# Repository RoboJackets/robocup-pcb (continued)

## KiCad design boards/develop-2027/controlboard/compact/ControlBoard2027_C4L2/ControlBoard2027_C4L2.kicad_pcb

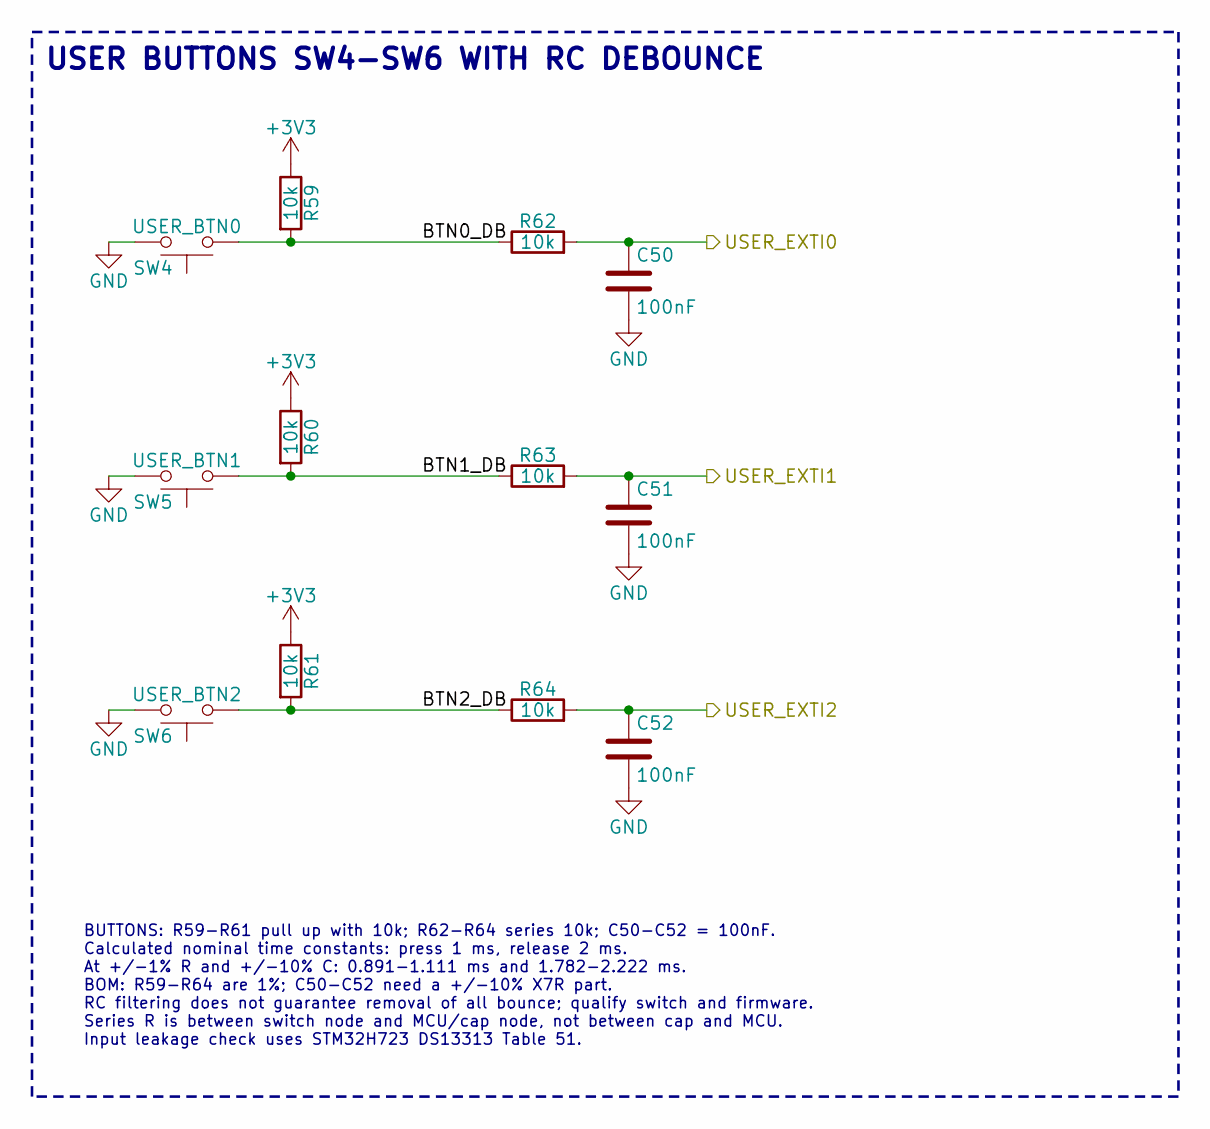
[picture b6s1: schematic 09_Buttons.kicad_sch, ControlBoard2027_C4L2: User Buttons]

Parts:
C50, C51, C52: 100nF; C_0402_1005Metric; Rating 16V X7R; MPN Samsung CL05B104KO5NNNC; LCSC C1525
R59, R60, R61, R62, R63, R64: 10k; R_0603_1608Metric; Rating 1%; MPN Panasonic ERJ-3EKF1002V; LCSC C25804
SW4: USER_BTN0; SW_PUSH_1P1T_6x3.5mm_H4.3_APEM_MJTP1243; MPN APEM MJTP1243; LCSC C2689636
SW5: USER_BTN1; SW_PUSH_1P1T_6x3.5mm_H4.3_APEM_MJTP1243; MPN APEM MJTP1243; LCSC C2689636
SW6: USER_BTN2; SW_PUSH_1P1T_6x3.5mm_H4.3_APEM_MJTP1243; MPN APEM MJTP1243; LCSC C2689636

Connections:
+3V3: R59.1, R60.1, R61.1; also elsewhere on the board
/MCU/USER_EXTI0: C50.1, R62.2; also elsewhere on the board
/MCU/USER_EXTI1: C51.1, R63.2; also elsewhere on the board
/MCU/USER_EXTI2: C52.1, R64.2; also elsewhere on the board
/User Buttons/BTN0_DB: R59.2, R62.1, SW4.1
/User Buttons/BTN1_DB: R60.2, R63.1, SW5.1
/User Buttons/BTN2_DB: R61.2, R64.1, SW6.1

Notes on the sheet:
BUTTONS: R59-R61 pull up with 10k; R62-R64 series 10k; C50-C52 = 100nF. Calculated nominal time constants: press 1 ms, release 2 ms. At +/-1% R and +/-10% C: 0.891-1.111 ms and 1.782-2.222 ms. BOM: R59-R64 are 1%; C50-C52 need a +/-10% X7R part. RC filtering does not guarantee removal of all bounce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
USER BUTTONS SW4-SW6 WITH RC DEBOUNCE

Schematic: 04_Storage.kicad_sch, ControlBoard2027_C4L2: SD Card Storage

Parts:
C1: 10uF; C_0603_1608Metric; Rating 10V X5R 10%; MPN Taiyo Yuden LMK107BBJ106MALT; LCSC C19702
C2: 100nF; C_0402_1005Metric; Rating 16V X7R; MPN Samsung CL05B104KO5NNNC; LCSC C1525
J1: microSD_SDIO; microSD_HC_Hirose_DM3AT-SF-PEJM5; MPN Hirose DM3AT-SF-PEJM5; LCSC C114218
R1, R2, R3, R4, R5, R73: 47k; R_0402_1005Metric; Rating 1%; MPN Yageo RC0402FR-0747KL; LCSC C25792
R6: 30R; R_0402_1005Metric; Rating 1%; MPN Stackpole RMCF0402FT30R0; LCSC C2479340
TP1: SD_CLK; TestPoint_Pad_1.0x1.0mm
U1: TPD6E05U06RVZ; Texas_R-PUSON-N14; MPN TPD6E05U06RVZR; LCSC C962978

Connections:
+3V3: C1.1, C2.1, J1.4 (VDD), R1.1, R2.1, R3.1, R4.1, R5.1, R73.1; also elsewhere on the board
/MCU/SDMMC_CK: R6.1; also elsewhere on the board
/MCU/SD_DET: J1.9 (DET_B), R73.2; also elsewhere on the board
/SD Card Storage/SDMMC_CMD: J1.3 (CMD), R3.2, U1.3 (NC), U1.12 (D2+); also elsewhere on the board
/SD Card Storage/SDMMC_D0: J1.7 (DAT0), R4.2, U1.6 (NC), U1.9 (D3+); also elsewhere on the board
/SD Card Storage/SDMMC_D1: J1.8 (DAT1), R5.2, U1.7 (NC), U1.8 (D3-); also elsewhere on the board
/SD Card Storage/SDMMC_D2: J1.1 (DAT2), R1.2, U1.1 (NC), U1.14 (D1+); also elsewhere on the board
/SD Card Storage/SDMMC_D3: J1.2 (DAT3/CD), R2.2, U1.2 (NC), U1.13 (D1-); also elsewhere on the board
/SD Card Storage/SD_CLK_CARD: J1.5 (CLK), R6.2, TP1.1 (1_1), U1.4 (NC), U1.11 (D2-)

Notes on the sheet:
SD ESD U1 AT J1, CLK TEST POINT
MICROSD J1 ON SDMMC2 4-BIT, CARD DETECT R73
SDMMC LAYOUT: review CLK, CMD and DAT0-3 as one timing interface. Routed 50R on L1 over L2 GND and on L4 over an L3 GND island; CLK/CMD/DAT0-3 67.08-67.66 mm incl. R6 (worst 0.47 mm vs CLK). Keep return paths continuous, short stubs and local J1 bypass capacitors. Use DS13313 SDMMC timing plus the 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
SD CARD: select an actual card MPN before final timing approval. Kingston SDCIT example: identification clock <=400 kHz, NOT 8 MHz. Higher transfer rates require successful initialization and timing validation. J1 Hirose DM3AT-SF-PEJM5. Shell to GND; power cannot be cycled independently. Card detec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
R6 = 30R provisional CLK source damping near PD6. CMD and DAT0-3 currently have no series damping; check both directions. 47k pull-ups are bias, not impedance termination. No data sheet establishes a constant 25R MCU output impedance.

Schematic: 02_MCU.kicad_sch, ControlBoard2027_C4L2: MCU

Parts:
C3, C4, C6, C8, C9, C10, C12, C13, C14, C15, C16, C17, C20, C21, C25, C27: 100nF; C_0402_1005Metric; Rating 16V X7R; MPN Samsung CL05B104KO5NNNC; LCSC C1525
C5: 10uF 10V X5R; C_0603_1608Metric; Rating 10V X5R 10%; MPN Taiyo Yuden LMK107BBJ106MALT; LCSC C19702
C7, C11: 4.7uF 16V X5R; C_0603_1608Metric; Rating 16V X5R; MPN TDK C1608X5R1C475K080AC; LCSC C19666
C18, C19: 12pF; C_0402_1005Metric; Rating 50V C0G; MPN Samsung CL05C120JB5NNNC; LCSC C1547
C22, C23: 2.2uF; C_0603_1608Metric; Rating 10V X7R; MPN Samsung CL10B225KP8NNNC; LCSC C100082
C24, C26: 1uF 50V X5R; C_0603_1608Metric; Rating 50V X5R; MPN Samsung CL10A105KP8NNNC; LCSC C15849
R7, R8, R9, R10, R14, R17, R18, R19: 2.2k; R_0402_1005Metric; Rating 1%; MPN Yageo RC0402FR-072K2L; LCSC C25879
R11, R13: 10k; R_0402_1005Metric; Rating 1%; MPN Yageo RC0402FR-0710KL; LCSC C25744
R12: 0R; R_0402_1005Metric; Rating 0R jumper; MPN Stackpole RMCF0402ZT0R00; LCSC C17168
R15, R16, R65, R66, R67, R68, R70, R71: 30R; R_0402_1005Metric; Rating 1%; MPN Stackpole RMCF0402FT30R0; LCSC C2479340
R20: 47k; R_0402_1005Metric; Rating 1%; MPN Yageo RC0402FR-0747KL; LCSC C25792
R21: 68k; R_0402_1005Metric; Rating 1%; MPN Vishay CRCW040268K0FKED; LCSC C482226
TP2: TP_VDDA; TestPoint_Pad_1.0x1.0mm
U2: STM32H723ZGT6; LQFP-144_20x20mm_P0.5mm; MPN ST STM32H723ZGT6; LCSC C730146
X1: 25MHz 10pF; Crystal_SMD_3225-4Pin_3.2x2.5mm; MPN Abracon ABM8-25.000MHZ-10-B1U-T; LCSC C5366868

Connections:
+3V3: C3.1, C4.1, C5.1, C6.1, C7.1, C8.1, C9.1, C10.1, C11.1, C12.1, C13.1, C14.1, C15.1, C16.1, C17.1, C21.1, C24.1, C25.1, C26.1, C27.1, R7.1, R8.1, R9.1, R10.1, R13.2, R14.1, R17.1, R18.1, R19.1, TP2.1 (1_1), U2.6 (VBAT), U2.17 (VDD), U2.30 (VDD), U2.32 (VREF+), U2.33 (VDDA), U2.39 (VDD), U2.52 (VDD), U2.62 (VDD), U2.72 (VDD), U2.84 (VDD), U2.95 (VDD33USB), U2.108 (VDD), U2.121 (VDD), U2.131 (VDD), U2.143 (PDR_ON), U2.144 (VDD); also elsewhere on the board
/DotStar LEDs/LED_SPI_MOSI: R71.1; also elsewhere on the board
/DotStar LEDs/LED_SPI_SCK: R70.1; also elsewhere on the board
/IMU/ACCEL_EXTI: U2.13 (PF3); also elsewhere on the board
/IMU/GYRO_EXTI: U2.12 (PF2); also elsewhere on the board
/IMU/IMU_I2C_SCL: R10.2, U2.81 (PD12); also elsewhere on the board
/IMU/IMU_I2C_SDA: R8.2, U2.82 (PD13); also elsewhere on the board
/MCU/BOOT0: R11.1, U2.138 (BOOT0); also elsewhere on the board
/MCU/DBG_UART_RX: U2.97 (PC7); also elsewhere on the board
/MCU/DBG_UART_TX: U2.96 (PC6); also elsewhere on the board
/MCU/DIP0: U2.58 (PE7); also elsewhere on the board
/MCU/DIP1: U2.59 (PE8); also elsewhere on the board
/MCU/DIP2: U2.60 (PE9); also elsewhere on the board
/MCU/DIP3: U2.63 (PE10); also elsewhere on the board
/MCU/DIP4: U2.67 (PE14); also elsewhere on the board
/MCU/DIP5: U2.68 (PE15); also elsewhere on the board
/MCU/DRIBBLER_SPI_CS: U2.115 (PD1); also elsewhere on the board
/MCU/ESP_DATA_READY: U2.136 (PB6); also elsewhere on the board
/MCU/ESP_HANDSHAKE: U2.137 (PB7); also elsewhere on the board
/MCU/ESP_MOSI_MCU: R66.1, U2.135 (PB5)
/MCU/ESP_RST: U2.142 (PE1); also elsewhere on the board
/MCU/ESP_SPI_CS: U2.132 (PG15); also elsewhere on the board
/MCU/ESP_SPI_MISO: U2.134 (PB4_NJTRST); also elsewhere on the board
/MCU/ESP_SPI_MOSI: R66.2; also elsewhere on the board
/MCU/ESP_SPI_SCK: R65.2; also elsewhere on the board
/MCU/EXPANSION_SCL: R7.2, U2.11 (PF1); also elsewhere on the board
/MCU/EXPANSION_SDA: R9.2, U2.10 (PF0); also elsewhere on the board
/MCU/KICKER_I2C_SCL: R14.2, U2.139 (PB8); also elsewhere on the board
/MCU/KICKER_I2C_SDA: R17.2, U2.140 (PB9); also elsewhere on the board
/MCU/LED_MOSI_MCU: R71.2, U2.43 (PA7)
/MCU/LED_SCK_MCU: R70.2, U2.41 (PA5)
/MCU/MOTOR0_SPI_CS: U2.114 (PD0); also elsewhere on the board
/MCU/MOTOR1_SPI_CS: U2.73 (PB12); also elsewhere on the board
/MCU/MOTOR2_SPI_CS: U2.77 (PD8); also elsewhere on the board
/MCU/MOTOR3_SPI_CS: U2.116 (PD2); also elsewhere on the board
/MCU/MOTOR_R_SPI_MISO: U2.75 (PB14); also elsewhere on the board
/MCU/MOTOR_R_SPI_MOSI: R68.2; also elsewhere on the board
/MCU/MOTOR_R_SPI_SCK: R67.2; also elsewhere on the board
/MCU/MOTOR_SPI_MISO: U2.112 (PC11); also elsewhere on the board
/MCU/MOTOR_SPI_MOSI: R16.2; also elsewhere on the board
/MCU/MOTOR_SPI_SCK: R15.2; also elsewhere on the board
/MCU/NRST: C20.1, U2.25 (NRST); also elsewhere on the board
/MCU/OLED_I2C_SCL: R18.2, U2.100 (PA8); also elsewhere on the board
/MCU/OLED_I2C_SDA: R19.2, U2.99 (PC9); also elsewhere on the board
/MCU/PWR_SRC_3V3: U2.3 (PE4); also elsewhere on the board
/MCU/PWR_SRC_5V: U2.4 (PE5); also elsewhere on the board
/MCU/PWR_UART_RX: U2.1 (PE2); also elsewhere on the board
/MCU/PWR_UART_TX: U2.2 (PE3); also elsewhere on the board
/MCU/SDMMC_CK: U2.122 (PD6); also elsewhere on the board
/MCU/SD_DET: U2.119 (PD5); also elsewhere on the board
/MCU/SWCLK: U2.109 (PA14_SWCLK); also elsewhere on the board
/MCU/SWDIO: U2.105 (PA13_SWDIO); also elsewhere on the board
/MCU/USER_EXTI0: U2.80 (PD11); also elsewhere on the board
/MCU/USER_EXTI1: U2.85 (PD14); also elsewhere on the board
/MCU/USER_EXTI2: U2.86 (PD15); also elsewhere on the board
/MCU/VBUS_SENSE: R20.2, R21.1, U2.101 (PA9)
/SD Card Storage/SDMMC_CMD: U2.123 (PD7); also elsewhere on the board
/SD Card Storage/SDMMC_D0: U2.124 (PG9); also elsewhere on the board
/SD Card Storage/SDMMC_D1: U2.125 (PG10); also elsewhere on the board
/SD Card Storage/SDMMC_D2: U2.126 (PG11); also elsewhere on the board
/SD Card Storage/SDMMC_D3: U2.127 (PG12); also elsewhere on the board
/USB and Debug/USB_DM: U2.103 (PA11); also elsewhere on the board
/USB and Debug/USB_DP: U2.104 (PA12); also elsewhere on the board
unnamed: C19.1, R12.1, X1.3
unnamed: C22.1, C23.1, U2.71 (VCAP), U2.106 (VCAP)
unnamed: R13.1, U2.110 (PA15_JTDI)
unnamed: R65.1, U2.133 (PB3_SWO)
unnamed: R67.1, U2.74 (PB13)
unnamed: R68.1, U2.76 (PB15)
unnamed: R15.1, U2.111 (PC10)
unnamed: R16.1, U2.113 (PC12)
unnamed: C18.1, U2.23 (PH0), X1.1
unnamed: R12.2, U2.24 (PH1)
VBUS: R20.1; also elsewhere on the board

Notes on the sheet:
VDD33USB p95 (C11+C13) USB FS PHY - keep both close
VDD p30
VBUS SENSE
MCU U2 STM32H723ZGT6 WITH ITS PIN-SIDE PARTS (VCAP, RESET / BOOT0, I2C PULL-UPS, SERIES R)
VDD p17
VDDA p33 (C24+C25)
VDD p131
HSE 25MHZ CRYSTAL
CLOCK: X1 = 25 MHz; set firmware clock tree to the fitted part. R12 = 0R is an oscillator drive-tuning link, not line termination. C18/C19 need measured stray capacitance to establish the 10 pF load. Startup margin and crystal drive remain unverified (ABM8, DS13313 HSE data). No blanket claim that 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
R15/R16 = 30R: provisional source damping, not certified matching. No fixed driver resistance or 55R target follows from DS13313 Tables 52/54. Validate SCK/MOSI/MISO/CS at every cable receiver, both directions.
VDD p84
VDDA p33 and VREF+ p32 use +3V3. Separate local bypass pairs; analog noise must be measured. Source: DS13313 supply scheme / electrical characteristics.
VDD p52
VBAT p6
VREF+ p32 (C26+C27)
VDD DECOUPLING (EACH CAP AT ITS PIN)
VDD p39
VDD p62
VDDA / VREF+ DECOUPLING
ROUTING - HSE CRYSTAL X1, C18, C19 within 5mm of PH0/PH1. Short equal OSC traces, GND guard ring. Nothing routed under or beside the loop.
I2C: R7/R9, R8/R10, R14/R17, R18/R19 are each 2.2k. At 3.3 V: (3.3-0.4)/2.2k = 1.32 mA sink requirement. For a 300 ns rise-time limit: C <= 300ns/(0.8473R) = 161 pF nominal. At +1% R: 159 pF. Include ESD, pins, cables and parallel pull-ups. LSM6DSV32X / SSD1306 / DS13313 timing and I/O data; extern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
VDD p108
ROUTING - DECOUPLING: each cap beside the STM32 pin named under it, via straight to GND. C22/C23 (VCAP) tight to p71/p106. The netlist does not keep this pairing.
VDD bulk (C5+C7) not pin-specific
ROUTING - MOTOR SPI (6 Mbit/s; SPI3 front J4/J8/J7, SPI2 rear J5/J6) R15/R16 within 5mm of PC10/PC12, R67/R68 of PB13/PB15, not at the connectors.
I2C VALIDATION REQUIRED: measure SDA and SCL at worst load. Change to 1.5k only if the rise time exceeds 300 ns, and recheck every device's VOL/current. OLED module pull-ups and expansion-device specifications are not established.
VDD p72
VDD p121
VDD p144

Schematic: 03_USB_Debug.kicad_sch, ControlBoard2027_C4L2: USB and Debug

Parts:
D1: TVS0500DRV; WSON-6-1EP_2x2mm_P0.65mm_EP1x1.6mm; MPN TI TVS0500DRVR; LCSC C609571
F1: PTC 0.75A 1812; Fuse_Bourns_MF-MSMF_1812; MPN Bourns MF-MSMF075/16X-2; LCSC C207065
J2: USB-C_DFU; USB_C_Receptacle_GCT_USB4110; MPN GCT USB4110-GF-A; LCSC C5143397
J3: STDC14; PinHeader_2x07_P1.27mm_Vertical_SMD; MPN Samtec FTSH-107-01-L-DV-K; LCSC C5307809
R22, R23: 5.1k; R_0402_1005Metric; Rating 1%; MPN Yageo RC0402FR-075K1L; LCSC C25905
SW1: RESET; SW_PUSH_1P1T_6x3.5mm_H4.3_APEM_MJTP1243; MPN APEM MJTP1243; LCSC C2689636
SW2: BOOT0_DFU; SW_PUSH_1P1T_6x3.5mm_H4.3_APEM_MJTP1243; MPN APEM MJTP1243; LCSC C2689636
TP3: TP_VBUS; TestPoint_Pad_1.0x1.0mm
U3: TPD4E05U06DQA; USON-10_2.5x1.0mm_P0.5mm; MPN TI TPD4E05U06DQAR; LCSC C138714

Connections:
+3V3: J3.3 (VCC), SW2.2; also elsewhere on the board
/MCU/BOOT0: SW2.1; also elsewhere on the board
/MCU/DBG_UART_RX: J3.13 (VCP_RX); also elsewhere on the board
/MCU/DBG_UART_TX: J3.14 (VCP_TX); also elsewhere on the board
/MCU/NRST: J3.12 (~RST), SW1.1; also elsewhere on the board
/MCU/SWCLK: J3.6 (JCLK/SWCLK); also elsewhere on the board
/MCU/SWDIO: J3.4 (JTMS/SWDIO); also elsewhere on the board
/USB and Debug/CC1: J2.A5 (CC1), R23.1
/USB and Debug/CC2: J2.B5 (CC2), R22.1
/USB and Debug/USB_DM: J2.A7 (D-), J2.B7 (D-), U3.2 (D1-), U3.5 (D2-), U3.6 (NC), U3.9 (NC); also elsewhere on the board
/USB and Debug/USB_DP: J2.A6 (D+), J2.B6 (D+), U3.1 (D1+), U3.4 (D2+), U3.7 (NC), U3.10 (NC); also elsewhere on the board
unnamed: D1.4 (IN), D1.5 (IN), D1.6 (IN), F1.2, J2.A4 (VBUS), J2.A9 (VBUS), J2.B4 (VBUS), J2.B9 (VBUS)
VBUS: F1.1, TP3.1 (1_1); also elsewhere on the board

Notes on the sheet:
USB LOAD: F1 PTC Ihold = 0.75 A at 20-23C, 0.55 A at 50C. Actual concurrent worst-case board/external current is not established. Restricted bench use until host current, startup and thermal budget are checked. F1 does not negotiate USB current; replacing it alone cannot approve more load.
USB-C J2: TVS, FUSE, CC RESISTORS, ESD
SWD is direct; damping depends on probe/cable edges and layout. DS13313 does not prescribe a universal 22R or 55R series resistor. NRST has an internal 30-50k pull-up; C20 = 100nF (DS13313 NRST data). U3 TPD4E05U06 has no supply pin (no rail injection); GND pins 3/8 to vias.
SWD: J3 STDC14; RESET AND BOOT BUTTONS
USB LAYOUT: keep DP/DM coupled over an uninterrupted ground reference. U3 flow-through at J2: A6/B6 (D+) and A7/B7 (D-) each pass U3 before any via; the duplicates join after U3. Impedance/skew depend on stackup, not series R. TPD4E05U06 layout: flow-through, short GND vias. 90R pair over L2 GND.

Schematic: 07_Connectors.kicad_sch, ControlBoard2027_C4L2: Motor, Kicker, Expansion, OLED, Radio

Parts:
C28: 22uF; C_0805_2012Metric; Rating 25V X5R 20%; MPN Samsung CL21A226MOQNNNE; LCSC C45783
C29: 100nF; C_0402_1005Metric; Rating 16V X7R; MPN Samsung CL05B104KO5NNNC; LCSC C1525
F3, F4: PTC 0.75A 1812; Fuse_Bourns_MF-MSMF_1812; MPN Bourns MF-MSMF075/16X-2; LCSC C207065
H1, H2, H3, H4: MountingHole; MountingHole_3.2mm_M3
H5, H6: MountingHole; MountingHole_2.2mm_M2
J4: MOTOR0; JST_GH_SM06B-GHS-TB_1x06-1MP_P1.25mm_Horizontal; MPN JST SM06B-GHS-TB(LF)(SN); LCSC C133065
J5: MOTOR1; JST_GH_SM06B-GHS-TB_1x06-1MP_P1.25mm_Horizontal; MPN JST SM06B-GHS-TB(LF)(SN); LCSC C133065
J6: MOTOR2; JST_GH_SM06B-GHS-TB_1x06-1MP_P1.25mm_Horizontal; MPN JST SM06B-GHS-TB(LF)(SN); LCSC C133065
J7: MOTOR3; JST_GH_SM06B-GHS-TB_1x06-1MP_P1.25mm_Horizontal; MPN JST SM06B-GHS-TB(LF)(SN); LCSC C133065
J8: DRIBBLER; JST_GH_SM06B-GHS-TB_1x06-1MP_P1.25mm_Horizontal; MPN JST SM06B-GHS-TB(LF)(SN); LCSC C133065
J9: RADIO_MEZZ; Samtec_LSHM-110-xx.x-x-DV-S_2x10-1SH_P0.50mm_Vertical_PIH; MPN Samtec LSHM-110-02.5-L-DV-A-S-K-TR; LCSC C3643542
J10: KICKER_I2C; JST_GH_SM04B-GHS-TB_1x04-1MP_P1.25mm_Horizontal; MPN JST SM04B-GHS-TB(LF)(SN); LCSC C189895
J11: EXP_1; JST_GH_SM08B-GHS-TB_1x08-1MP_P1.25mm_Horizontal; MPN JST SM08B-GHS-TB(LF)(SN); LCSC C265111
J12: EXP_2; JST_GH_SM08B-GHS-TB_1x08-1MP_P1.25mm_Horizontal; MPN JST SM08B-GHS-TB(LF)(SN); LCSC C265111
J13: OLED; OLED_0.96in_SSD1306_I2C_Module_Socket_1x04_P2.54mm; MPN BOOMELE 2.54-1*4P; LCSC C2718488
R24, R25, R26, R27, R28, R29, R32: 10k; R_0402_1005Metric; Rating 1%; MPN Yageo RC0402FR-0710KL; LCSC C25744
R30, R31, R69: 100k; R_0402_1005Metric; Rating 1%; MPN Yageo RC0402FR-07100KL; LCSC C25741
TP4: SCK; TestPoint_Pad_1.0x1.0mm
TP5: MOSI; TestPoint_Pad_1.0x1.0mm
TP6: MISO; TestPoint_Pad_D1.0mm
TP7: KICK_SCL; TestPoint_Pad_1.0x1.0mm
TP8: EXP_SCL; TestPoint_Pad_1.0x1.0mm
TP9: GND; TestPoint_Pad_1.0x1.0mm
U4, U5, U6, U12, U13, U14, U16, U17: TPD4E05U06DQA; USON-10_2.5x1.0mm_P0.5mm; MPN TI TPD4E05U06DQAR; LCSC C138714

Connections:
+3V3: C28.1, C29.1, J9.15, J9.17, J9.19, J13.2, R24.2, R25.2, R26.2, R27.2, R28.2, R29.2; also elsewhere on the board
+5V: F3.2, F4.2; also elsewhere on the board
/MCU/DRIBBLER_SPI_CS: J8.6, R28.1, U14.5 (D2-), U14.6 (NC); also elsewhere on the board
/MCU/ESP_DATA_READY: J9.12, R32.1; also elsewhere on the board
/MCU/ESP_HANDSHAKE: J9.10, R31.1; also elsewhere on the board
/MCU/ESP_RST: J9.20; also elsewhere on the board
/MCU/ESP_SPI_CS: J9.2, R29.1; also elsewhere on the board
/MCU/ESP_SPI_MISO: J9.16; also elsewhere on the board
/MCU/ESP_SPI_MOSI: J9.4; also elsewhere on the board
/MCU/ESP_SPI_SCK: J9.8; also elsewhere on the board
/MCU/EXPANSION_SCL: J11.6, J12.6, TP8.1 (1_1), U6.1 (D1+), U6.10 (NC), U16.1 (D1+), U16.10 (NC); also elsewhere on the board
/MCU/EXPANSION_SDA: J11.8, J12.8, U6.2 (D1-), U6.9 (NC), U16.2 (D1-), U16.9 (NC); also elsewhere on the board
/MCU/KICKER_I2C_SCL: J10.3, TP7.1 (1_1), U17.4 (D2+), U17.7 (NC); also elsewhere on the board
/MCU/KICKER_I2C_SDA: J10.1, U17.1 (D1+), U17.10 (NC); also elsewhere on the board
/MCU/MOTOR0_SPI_CS: J4.6, R24.1, U4.5 (D2-), U4.6 (NC); also elsewhere on the board
/MCU/MOTOR1_SPI_CS: J5.6, R25.1, U5.5 (D2-), U5.6 (NC); also elsewhere on the board
/MCU/MOTOR2_SPI_CS: J6.6, R26.1, U12.5 (D2-), U12.6 (NC); also elsewhere on the board
/MCU/MOTOR3_SPI_CS: J7.6, R27.1, U13.5 (D2-), U13.6 (NC); also elsewhere on the board
/MCU/MOTOR_R_SPI_MISO: J5.3, J6.3, U5.2 (D1-), U5.9 (NC), U12.2 (D1-), U12.9 (NC); also elsewhere on the board
/MCU/MOTOR_R_SPI_MOSI: J5.1, J6.1, U5.1 (D1+), U5.10 (NC), U12.1 (D1+), U12.10 (NC); also elsewhere on the board
/MCU/MOTOR_R_SPI_SCK: J5.4, J6.4, R69.1, U5.4 (D2+), U5.7 (NC), U12.4 (D2+), U12.7 (NC); also elsewhere on the board
/MCU/MOTOR_SPI_MISO: J4.3, J7.3, J8.3, TP6.1 (1_1), U4.2 (D1-), U4.9 (NC), U13.2 (D1-), U13.9 (NC), U14.2 (D1-), U14.9 (NC); also elsewhere on the board
/MCU/MOTOR_SPI_MOSI: J4.1, J7.1, J8.1, TP5.1 (1_1), U4.1 (D1+), U4.10 (NC), U13.1 (D1+), U13.10 (NC), U14.1 (D1+), U14.10 (NC); also elsewhere on the board
/MCU/MOTOR_SPI_SCK: J4.4, J7.4, J8.4, R30.1, TP4.1 (1_1), U4.4 (D2+), U4.7 (NC), U13.4 (D2+), U13.7 (NC), U14.4 (D2+), U14.7 (NC); also elsewhere on the board
/MCU/OLED_I2C_SCL: J13.3; also elsewhere on the board
/MCU/OLED_I2C_SDA: J13.4; also elsewhere on the board
/Motor, Kicker, Expansion, OLED, Radio/+5V_EXT1: F3.1, J11.3, J11.4
/Motor, Kicker, Expansion, OLED, Radio/+5V_EXT2: F4.1, J12.3, J12.4

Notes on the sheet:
0.96in 4-pin module, I2C 0x3C, on a 1x04 socket. Module pull-ups add in parallel to R18/R19.
ESD AT CONNECTORS U4-U6
M2 SPEAKER HOLES H5-H6
M3 CORNER HOLES H1-H4
SPI ROUTING: the motor and dribbler buses are 50 ohm lines, on L1 over the L2 GND plane and on L4 over L3 GND regions (DESIGN_NOTES section 12.3). R15/R16 (SPI3) and R67/R68 (SPI2) are source damping at the MCU; verify every multidrop endpoint. ESD arrays sit at the connectors (flow-through, GND pa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
J9 = 30x40 radio J2 (Inboard / Overhang), LSHM-110-02.5 on both (5mm stack). Even row: 2 CS, 4 MOSI, 8 SCK, 10 HANDSHAKE, 12 DATA_READY, 16 MISO, 20 RST; 6/14/18 GND. Odd row: 1-13 GND, 15/17/19 +3V3. SH to GND. Face to face, pin p here mates radio pin p+1 (odd p) or p-1 (even p). The radio sits ov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
CS PULL-UPS / PULL-DOWNS
MOTOR MODULES J4-J8
OLED J13 (SSD1306)
I2C CONNECTORS: J10 KICKER (SIGNALS ONLY), J11/J12 FED BY F3/F4
RADIO LINK J9 (SAMTEC LSHM MEZZANINE)
ESD AT CONNECTORS U12-U14, U16, U17
SCOPE TEST POINTS
CONNECTOR BUS AND POWER NOTES

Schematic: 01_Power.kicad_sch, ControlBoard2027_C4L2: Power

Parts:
C30: 2.2uF 16V X5R; C_0603_1608Metric; Rating 16V X5R; MPN Samsung CL10A225KO8NNNC; LCSC C23630
C31: 4.7uF; C_0603_1608Metric; Rating 16V X5R; MPN TDK C1608X5R1C475K080AC; LCSC C19666
C32: 10uF 10V X5R; C_0603_1608Metric; Rating 10V X5R 10%; MPN Taiyo Yuden LMK107BBJ106MALT; LCSC C19702
C33, C37: 22uF; C_0805_2012Metric; Rating 25V X5R 20%; MPN Samsung CL21A226MOQNNNE; LCSC C45783
C34: 10uF; C_0603_1608Metric; Rating 10V X5R 10%; MPN Taiyo Yuden LMK107BBJ106MALT; LCSC C19702
C35: 2.2uF 16V X7R; C_0805_2012Metric; Rating 16V X7R; MPN Samsung CL21B225KOFNNNE; LCSC C28234
C36: 2.2uF 10V X7R; C_0603_1608Metric; Rating 10V X7R; MPN Samsung CL10B225KP8NNNC; LCSC C100082
C38: 22uF; C_0603_1608Metric; Rating 6.3V X5R 20%; MPN Taiyo Yuden JMK107BBJ226MA-T; LCSC C59461
C39, C40: 100nF; C_0402_1005Metric; Rating 16V X7R; MPN Samsung CL05B104KO5NNNC; LCSC C1525
D2: 10V; D_SOD-323; MPN Nexperia BZX384-C10,115; LCSC C96228
D3, D4: TVS0500DRV; WSON-6-1EP_2x2mm_P0.65mm_EP1x1.6mm; MPN TI TVS0500DRVR; LCSC C609571
D5: RED_5V; LED_0603_1608Metric; MPN Kingbright APT1608EC; LCSC C5554143
D6: RED_3V3; LED_0603_1608Metric; MPN Kingbright APT1608EC; LCSC C5554143
F5, F6: PTC 1.25A 1812; Fuse_Bourns_MF-MSMF_1812; MPN Bourns MF-MSMF125/16X-2; LCSC C207067
J15: PB 7P; JST_PH_S7B-PH-K_1x07_P2.00mm_Horizontal; MPN JST S7B-PH-K-S(LF)(SN); LCSC C157917
Q1: AO3401A; SOT-23; MPN AOS AO3401A; LCSC C15127
R33, R34: 1k; R_0402_1005Metric; Rating 1%; MPN Yageo RC0402FR-071KL; LCSC C11702
R35, R36, R38: 100k; R_0603_1608Metric; Rating 1%; MPN Yageo RC0603FR-07100KL; LCSC C25803
R37: 36k; R_0603_1608Metric; Rating 1%; MPN Yageo RC0603FR-0736KL; LCSC C114619
R39: 68k; R_0603_1608Metric; Rating 1%; MPN Yageo RC0603FR-0768KL; LCSC C23231
R40, R41: 1M; R_0603_1608Metric; Rating 1%; MPN Yageo RC0603FR-071ML; LCSC C22935
R42, R43, R44: 10k; R_0603_1608Metric; Rating 1%; MPN Panasonic ERJ-3EKF1002V; LCSC C25804
R45: 3.3k; R_0603_1608Metric; Rating 1%; MPN Yageo RC0603FR-073K3L; LCSC C22978
R46: 1.5k; R_0603_1608Metric; Rating 1%; MPN Yageo RC0603FR-071K5L; LCSC C22843
TP10: PWR_UART_TX; TestPoint_Pad_1.0x1.0mm
TP11: PWR_UART_RX; TestPoint_Pad_1.0x1.0mm
TP12: TP_GND; TestPoint_Pad_1.0x1.0mm
TP13: 5V_PROT; TestPoint_Pad_1.0x1.0mm
TP14: 3V3_RAW; TestPoint_Pad_1.0x1.0mm
TP15: TP_3V3_LDO; TestPoint_Pad_1.0x1.0mm
TP16: TP_+5V; TestPoint_Pad_1.0x1.0mm
TP17: TP_+3V3; TestPoint_Pad_1.0x1.0mm
U7: MCP1826S-3302E; SOT-223-3_TabPin2; Rating 1A, VIN 6.0V max, 3.3V +-2.5%; MPN Microchip MCP1826S-3302E/DB; LCSC C638624
U8, U9: TPS2116DRL; TI_TPS2116_DRL0008A; MPN TI TPS2116DRLR; LCSC C3235557

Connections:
+3V3: C38.1, C40.1, R42.1, R43.1, R46.1, TP17.1 (1_1), U9.2 (VOUT), U9.7 (VOUT); also elsewhere on the board
+5V: C37.1, C39.1, R45.1, TP16.1 (1_1), U8.2 (VOUT), U8.7 (VOUT); also elsewhere on the board
/MCU/PWR_SRC_3V3: R41.2, R43.2, U9.8 (ST); also elsewhere on the board
/MCU/PWR_SRC_5V: R44.2; also elsewhere on the board
/MCU/PWR_UART_RX: R34.2, TP11.1 (1_1); also elsewhere on the board
/MCU/PWR_UART_TX: R33.2, TP10.1 (1_1); also elsewhere on the board
/Power/+3V3_LDO: C32.1, C36.1, TP15.1 (1_1), U7.3 (VO), U9.6 (VIN2)
/Power/+3V3_RAW: D4.4 (IN), D4.5 (IN), D4.6 (IN), F6.2, J15.4, TP14.1 (1_1)
/Power/+5V_PROT: D2.1 (K), D3.4 (IN), D3.5 (IN), D3.6 (IN), F5.2, Q1.2 (S), TP13.1 (1_1)
/Power/+5V_RAW: J15.6, Q1.3 (D)
/Power/AUTO3: R38.2, R39.1, R41.1, U9.4 (PR1)
/Power/AUTO5: R36.2, R37.1, R40.1, U8.4 (PR1)
unnamed: D2.2 (A), Q1.1 (G), R35.1
unnamed: D5.2 (A), R45.2
unnamed: D6.2 (A), R46.2
unnamed: J15.1, R33.1
unnamed: J15.2, R34.1
unnamed: R40.2, R42.2, R44.1, U8.8 (ST)
VBUS: C30.1, C31.1, C35.1, U7.1 (VI), U8.6 (VIN2); also elsewhere on the board

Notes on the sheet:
POWER LAYOUT: PCB routed; thermal verification pending. Minimize TVS return inductance; input/output caps close to U8/U9. Size copper from actual load, temperature and stackup, not a fixed 1 mm rule. TPS2116 section 10; MCP1826S thermal data; TVS0500 layout guidance.
3V3 MUX U9: POWERBOARD > USB LDO AUTO
USB INPUT: C30 + C31 + C35 = 9.1uF on VBUS (USB limit 10uF). PTC rating is not USB-current permission. USB 3V3 comes from U7 LDO via U9. Sources: TPS2116 7.3.2; MF-MSMF / 1812L; MCP1826S.
R36/R37 + R40: AUTO ~3.55 V fall / 3.88 V rise (VREF 1.00 V) only with 3.3 V ST bias. VREF tolerance is +/-8%: fall 3.24-3.86 V.
D2: BZX384-C10 gate clamp; characterize transients. 10 V rating is tested at 5 mA, not the R35 bias current.
J15 JST PH 7P: 1 TX (MCU->PB), 2 RX (PB->MCU), 3/5/7 GND, 4 +3V3, 6 +5V. PH contact 2 A: +5V_RAW has one pin, so 2 A is the 5 V input limit. R33/R34 1k limit current if TX/RX meet a driven line; not power-off isolation. Q1 reverse-polarity FET on 5V only; no 3V3 reverse-polarity FET. PTC faults and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
5V INPUT: Q1 REVERSE POLARITY, D3 TVS, F5 FUSE
5V MUX U8: POWERBOARD > USB AUTO
PROTECTION LIMITS: TVS0500 clamps up to 9.2 V at 43 A. This is NOT proof of protection for 6 V-absolute-max TPS2116 or 3V3 loads. PTCs are thermal devices, not fast current limits; verify fault coordination. Sources: TVS0500, TPS2116 absolute ratings, MF-MSMF / 1812L.
3V3 INPUT: D4 TVS, F6 FUSE
USB VBUS AND 3V3 LDO U7
POWERBOARD CONNECTOR J15
R38/R39 + R41: ST pull-up is +3V3, which tracks VIN1 while selected. Nominal fall ~2.34 V, rise ~2.57 V; NOT rail-valid detection.

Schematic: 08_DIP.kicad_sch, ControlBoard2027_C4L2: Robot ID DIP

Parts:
R53, R54, R55, R56, R57, R58: 100k; R_0603_1608Metric; Rating 1%; MPN Yageo RC0603FR-07100KL; LCSC C25803
SW3: DIP_6pos_ROBOT_ID; SW_DIP_SPSTx06_Slide_6.7x16.8mm_W7.62mm_P2.54mm_LowProfile; MPN CTS 209-6MS; LCSC C129072

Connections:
+3V3: R53.1, R54.1, R55.1, R56.1, R57.1, R58.1; also elsewhere on the board
/MCU/DIP0: R53.2, SW3.1; also elsewhere on the board
/MCU/DIP1: R54.2, SW3.2; also elsewhere on the board
/MCU/DIP2: R55.2, SW3.3; also elsewhere on the board
/MCU/DIP3: R56.2, SW3.4; also elsewhere on the board
/MCU/DIP4: R57.2, SW3.5; also elsewhere on the board
/MCU/DIP5: R58.2, SW3.6; also elsewhere on the board

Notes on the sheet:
DIP R53-R58 = 100k: STM32 250 nA input leakage gives 25 mV drop nominal. Logic bias is adequate for an unloaded MCU input (DS13313 Table 51). DIP switch: verify minimum contact load; 33 uA is not proof. Debounce/sample stability needs firmware; no universal 100nF requirement.
ROBOT ID DIP SWITCH SW3 (100K PULL-UPS)

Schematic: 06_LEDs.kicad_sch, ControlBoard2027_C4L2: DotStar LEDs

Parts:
C41, C43, C44, C45, C46, C47: 100nF; C_0402_1005Metric; Rating 16V X7R; MPN Samsung CL05B104KO5NNNC; LCSC C1525
C42: 22uF 25V X5R; C_0805_2012Metric; Rating 25V X5R 20%; MPN Samsung CL21A226MOQNNNE; LCSC C45783
D7, D8, D9, D10, D11: SK9822-EC20; OPSCO_SK9822-EC20; MPN OPSCO SK9822-EC20; LCSC C2909059
R47, R48: 100k; R_0402_1005Metric; Rating 1%; MPN Yageo RC0402FR-07100KL; LCSC C25741
TP18: LED_SDI_IN; TestPoint_Pad_1.0x1.0mm
TP19: LED_CKI_IN; TestPoint_Pad_1.0x1.0mm
TP20: TP_LED_SDO; TestPoint_Pad_1.0x1.0mm
TP21: TP_LED_CKO; TestPoint_Pad_1.0x1.0mm
U10: 74AHCT125; SO-14_3.9x8.65mm_P1.27mm; MPN TI SN74AHCT125DR; LCSC C155176

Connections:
+5V: C41.1, C42.1, C43.1, C44.1, C45.1, C46.1, C47.1, D7.5 (VDD), D8.5 (VDD), D9.5 (VDD), D10.5 (VDD), D11.5 (VDD), U10.10, U10.13, U10.14 (VCC); also elsewhere on the board
/DotStar LEDs/LED_SPI_MOSI: R47.1, U10.5; also elsewhere on the board
/DotStar LEDs/LED_SPI_SCK: R48.1, U10.2; also elsewhere on the board
unnamed: D7.4 (CKI), TP19.1 (1_1), U10.3
unnamed: D7.6 (CKO), D8.4 (CKI)
unnamed: D7.3 (SDI), TP18.1 (1_1), U10.6
unnamed: D7.1 (SDO), D8.3 (SDI)
unnamed: D8.6 (CKO), D9.4 (CKI)
unnamed: D8.1 (SDO), D9.3 (SDI)
unnamed: D9.6 (CKO), D10.4 (CKI)
unnamed: D10.6 (CKO), D11.4 (CKI)
unnamed: D9.1 (SDO), D10.3 (SDI)
unnamed: D10.1 (SDO), D11.3 (SDI)
unnamed: D11.6 (CKO), TP21.1 (1_1)
unnamed: D11.1 (SDO), TP20.1 (1_1)

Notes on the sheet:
LED LEVEL SHIFT: U10 SN74AHCT125, rated VCC 4.5-5.5 V. TTL inputs: 3.3 V MCU levels are valid. R47/R48 100k hold the inputs low at reset; unused gates 3/4 disabled. D7-D11 SK9822-EC20 (alt. BB-2020BGR-TRB). On USB, +5V can sit below 4.5 V. Firmware LED current caps are requirements. TP18/19 chain i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
LEVEL SHIFT U10 (3.3V SPI TO 5V)
U10 SPARE GATES
DOTSTAR CHAIN D7-D11 AND DECOUPLING
ROUTING - DOTSTARS U10 -> D7 CLK/DATA short and routed together, over GND. LED-to-LED CO->CI and DO->DI as matched pairs. C43-C47 at each LED VDD pin. C42 where +5V enters the chain. LEDs in the 5-dot shell pattern.

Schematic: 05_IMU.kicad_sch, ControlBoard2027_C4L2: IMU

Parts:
C48, C49: 100nF; C_0402_1005Metric; Rating 16V X7R; MPN Samsung CL05B104KO5NNNC; LCSC C1525
U11: LSM6DSV32X; ST_LGA-14L_2.5x3mm_P0.5mm; MPN ST LSM6DSV32XTR; LCSC C22461202

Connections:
+3V3: C48.1, C49.1, U11.5 (VDDIO), U11.8 (VDD), U11.12 (CS); also elsewhere on the board
/IMU/ACCEL_EXTI: U11.4 (INT1); also elsewhere on the board
/IMU/GYRO_EXTI: U11.9 (INT2); also elsewhere on the board
/IMU/IMU_I2C_SCL: U11.13 (SCL); also elsewhere on the board
/IMU/IMU_I2C_SDA: U11.14 (SDA); also elsewhere on the board

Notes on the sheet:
ROUTING - IMU C48 (VDDIO pin 5), C49 (VDD pin 8): 100nF, as close to the pins as possible. CS to VDDIO = I2C. SA0, SDx, SCx to GND: address 0x6A, mode 1 (DS13511 Fig. 28). OCS_aux/SDO_aux open. No traces or vias under the package.
IMU U11 LSM6DSV32X: I2C (0x6A), INT1/INT2 INTERRUPTS
INTERRUPTS: INT1 -> ACCEL_EXTI (PF3), INT2 -> GYRO_EXTI (PF2). Both are push-pull and are driven low from power-up (DS13511 Table 23), so no pull-downs are fitted. Route data-ready or events to them with INT1_CTRL/INT2_CTRL.

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
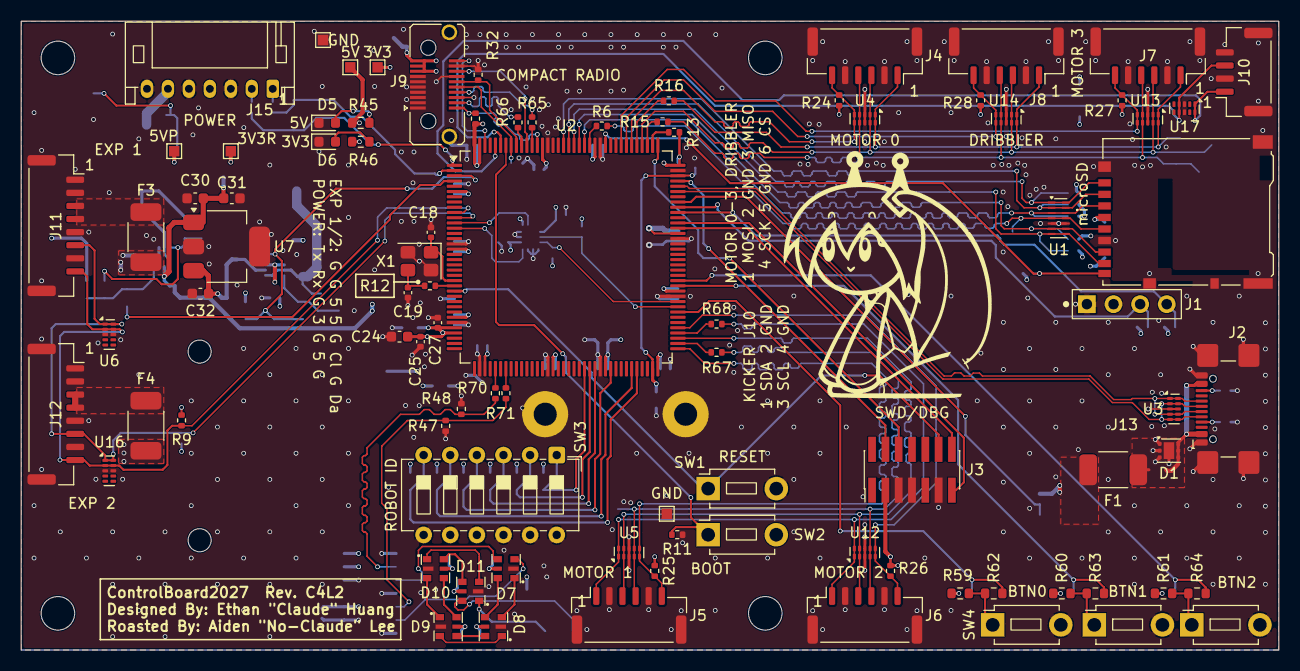
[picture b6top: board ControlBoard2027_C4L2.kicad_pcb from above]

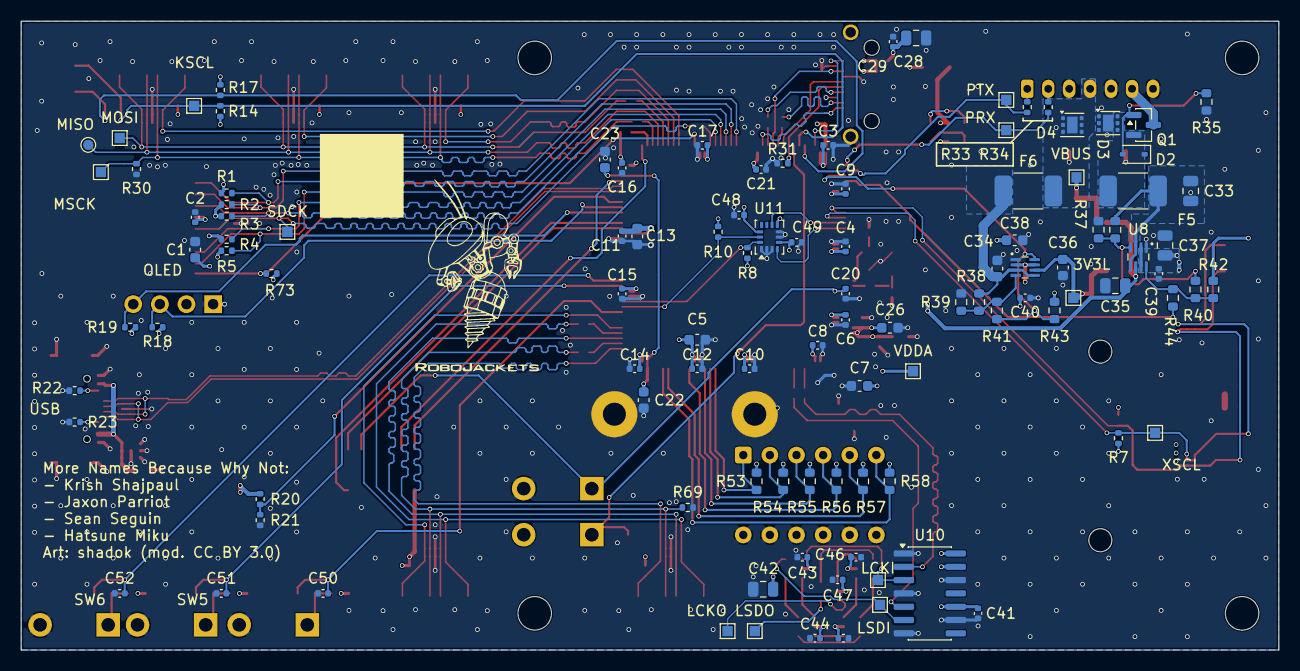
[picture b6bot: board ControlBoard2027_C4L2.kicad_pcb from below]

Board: 4 copper layers, 120.0 x 60.0 mm, 204 parts (108 on the bottom side), 111 nets.

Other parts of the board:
G1: GRAPHIC_ROBOJACKET_LOGO
HR1, HR2: Radio standoff M2; MountingHole_2.2mm_M2_Pad

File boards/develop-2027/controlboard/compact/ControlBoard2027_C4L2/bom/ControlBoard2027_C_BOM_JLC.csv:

Comment,Designator,Footprint,LCSC Part #
10uF / 10uF 10V X5R,"C1,C5,C32,C34",C_0603_1608Metric,C19702
100nF,"C2,C3,C4,C6,C8,C9,C10,C12,C13,C14,C15,C16,C17,C20,C21,C25,C27,C29,C39,C40,C41,C43,C44,C45,C46,C47,C48,C49,C50,C51,C52",C_0402_1005Metric,C1525
4.7uF 16V X5R / 4.7uF,"C7,C11,C31",C_0603_1608Metric,C19666
12pF,"C18,C19",C_0402_1005Metric,C1547
2.2uF / 2.2uF 10V X7R,"C22,C23,C36",C_0603_1608Metric,C100082
1uF 50V X5R,"C24,C26",C_0603_1608Metric,C15849
22uF / 22uF 25V X5R,"C28,C33,C37,C42",C_0805_2012Metric,C45783
2.2uF 16V X5R,C30,C_0603_1608Metric,C23630
2.2uF 16V X7R,C35,C_0805_2012Metric,C28234
22uF,C38,C_0603_1608Metric,C59461
TVS0500DRV,"D1,D3,D4",WSON-6-1EP_2x2mm_P0.65mm_EP1x1.6mm,C609571
10V,D2,D_SOD-323,C96228
RED_5V / RED_3V3,"D5,D6",LED_0603_1608Metric,C5554143
SK9822-EC20,"D7,D8,D9,D10,D11",OPSCO_SK9822-EC20,C2909059
PTC 0.75A 1812,"F1,F3,F4",Fuse_Bourns_MF-MSMF_1812,C207065
PTC 1.25A 1812,"F5,F6",Fuse_Bourns_MF-MSMF_1812,C207067
microSD_SDIO,J1,microSD_HC_Hirose_DM3AT-SF-PEJM5,C114218
USB-C_DFU,J2,USB_C_Receptacle_GCT_USB4110,C5143397
STDC14,J3,PinHeader_2x07_P1.27mm_Vertical_SMD,C5307809
MOTOR0 / MOTOR1 / MOTOR2 / MOTOR3 / DRIBBLER,"J4,J5,J6,J7,J8",JST_GH_SM06B-GHS-TB_1x06-1MP_P1.25mm_Horizontal,C133065
RADIO_MEZZ,J9,Samtec_LSHM-110-xx.x-x-DV-S_2x10-1SH_P0.50mm_Vertical_PIH,C3643542
KICKER_I2C,J10,JST_GH_SM04B-GHS-TB_1x04-1MP_P1.25mm_Horizontal,C189895
EXP_1 / EXP_2,"J11,J12",JST_GH_SM08B-GHS-TB_1x08-1MP_P1.25mm_Horizontal,C265111
OLED,J13,OLED_0.96in_SSD1306_I2C_Module_Socket_1x04_P2.54mm,C2718488
PB 7P,J15,JST_PH_S7B-PH-K_1x07_P2.00mm_Horizontal,C157917
AO3401A,Q1,SOT-23,C15127
47k,"R1,R2,R3,R4,R5,R20,R73",R_0402_1005Metric,C25792
30R,"R6,R15,R16,R65,R66,R67,R68,R70,R71",R_0402_1005Metric,C2479340
2.2k,"R7,R8,R9,R10,R14,R17,R18,R19",R_0402_1005Metric,C25879
10k,"R11,R13,R24,R25,R26,R27,R28,R29,R32",R_0402_1005Metric,C25744
0R,R12,R_0402_1005Metric,C17168
68k,R21,R_0402_1005Metric,C482226
5.1k,"R22,R23",R_0402_1005Metric,C25905
100k,"R30,R31,R47,R48,R69",R_0402_1005Metric,C25741
1k,"R33,R34",R_0402_1005Metric,C11702
100k,"R35,R36,R38,R53,R54,R55,R56,R57,R58",R_0603_1608Metric,C25803
36k,R37,R_0603_1608Metric,C114619
68k,R39,R_0603_1608Metric,C23231
1M,"R40,R41",R_0603_1608Metric,C22935
10k,"R42,R43,R44,R59,R60,R61,R62,R63,R64",R_0603_1608Metric,C25804
3.3k,R45,R_0603_1608Metric,C22978
1.5k,R46,R_0603_1608Metric,C22843
RESET / BOOT0_DFU / USER_BTN0 / USER_BTN1 / USER_BTN2,"SW1,SW2,SW4,SW5,SW6",SW_PUSH_1P1T_6x3.5mm_H4.3_APEM_MJTP1243,C2689636
DIP_6pos_ROBOT_ID,SW3,SW_DIP_SPSTx06_Slide_6.7x16.8mm_W7.62mm_P2.54mm_LowProfile,C129072
TPD6E05U06RVZ,U1,Texas_R-PUSON-N14,C962978
STM32H723ZGT6,U2,LQFP-144_20x20mm_P0.5mm,C730146
TPD4E05U06DQA,"U3,U4,U5,U6,U12,U13,U14,U16,U17",USON-10_2.5x1.0mm_P0.5mm,C138714
MCP1826S-3302E,U7,SOT-223-3_TabPin2,C638624
TPS2116DRL,"U8,U9",TI_TPS2116_DRL0008A,C3235557
74AHCT125,U10,SO-14_3.9x8.65mm_P1.27mm,C155176
LSM6DSV32X,U11,ST_LGA-14L_2.5x3mm_P0.5mm,C22461202
25MHz 10pF,X1,Crystal_SMD_3225-4Pin_3.2x2.5mm,C5366868
